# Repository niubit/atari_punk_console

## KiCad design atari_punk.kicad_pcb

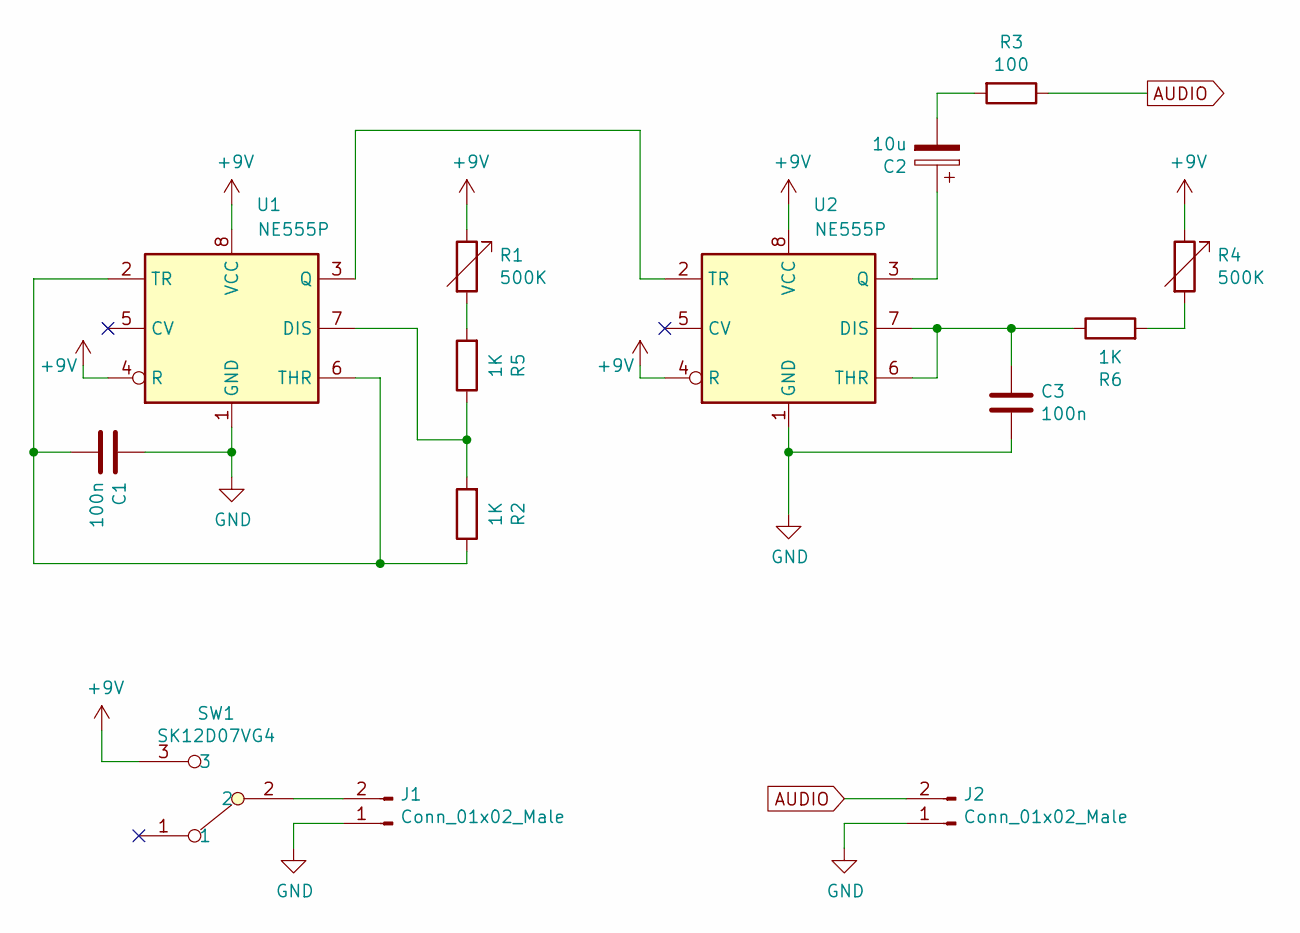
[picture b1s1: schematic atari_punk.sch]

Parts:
C1, C3: 100n; C_Disc_D4.3mm_W1.9mm_P5.00mm
C2: 10u; CP_Radial_D5.0mm_P2.50mm
J1, J2: Conn_01x02_Male; PinHeader_1x02_P2.54mm_Vertical
R1, R4: 500K; Potentiometer_Alpha_RD901F-40-00D_Single_Vertical_mod
R2, R5, R6: 1K; R_Axial_DIN0207_L6.3mm_D2.5mm_P10.16mm_Horizontal
R3: 100; R_Axial_DIN0207_L6.3mm_D2.5mm_P10.16mm_Horizontal
SW1: SK12D07VG4; SW_CuK_OS102011MA1QN1_SPDT_Angled
U1, U2: NE555P; DIP-8_W7.62mm

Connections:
+9V: R1.1, R4.1, SW1.3, U1.4 (R), U1.8 (VCC), U2.4 (R), U2.8 (VCC)
AUDIO: J2.2, R3.1
GND: C1.1, C3.2, J1.1, J2.1, U1.1 (GND), U2.1 (GND)
unnamed: C1.2, R2.1, U1.2 (TR), U1.6 (THR)
unnamed: C2.1, U2.3 (Q)
unnamed: C2.2, R3.2
unnamed: C3.1, R6.1, U2.6 (THR), U2.7 (DIS)
unnamed: J1.2, SW1.2
unnamed: R1.2, R5.2
unnamed: R2.2, R5.1, U1.7 (DIS)
unnamed: R4.2, R6.2
unnamed: U1.3 (Q), U2.2 (TR)

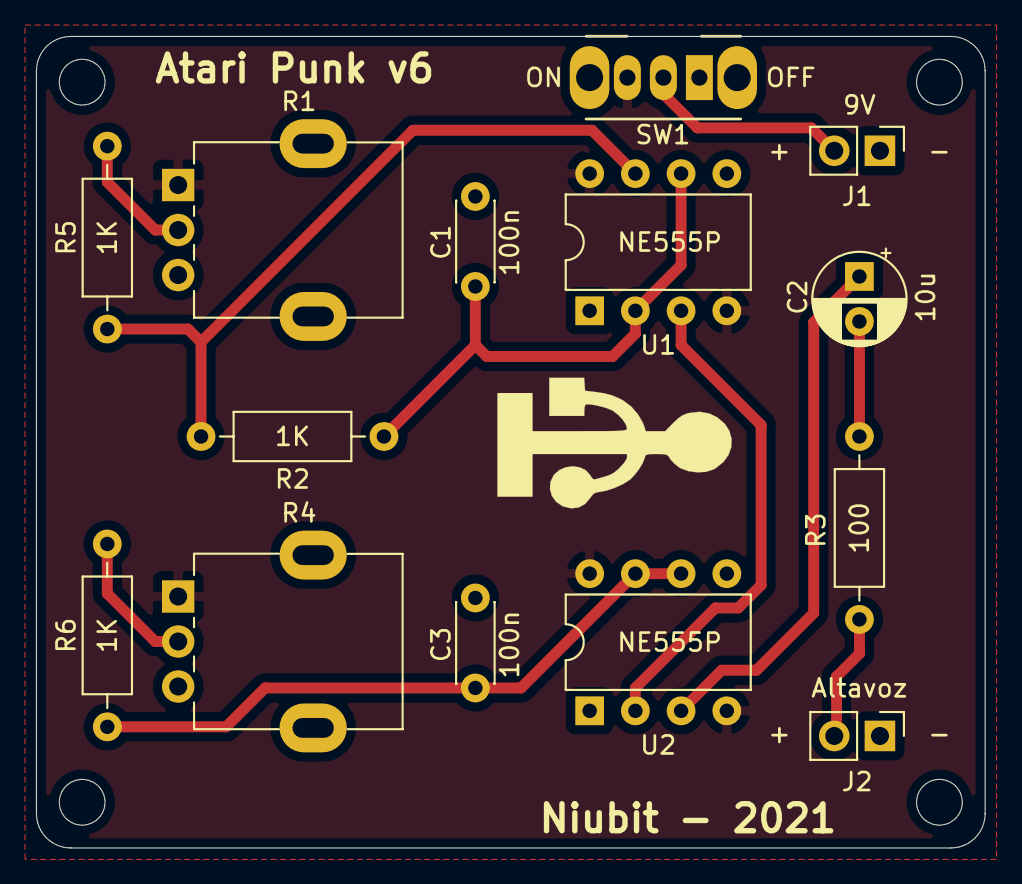
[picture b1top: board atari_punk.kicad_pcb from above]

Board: 2 copper layers, 52.7 x 45.1 mm, 14 parts (0 on the bottom side), 12 nets.

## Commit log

2020-12-28 Initial commit.
2020-12-28 Adding BOM.
2020-12-28 Update BOM.
2021-04-26 Changed Niubit logo.
2021-04-27 Added resistors. Added big Niubit logo. Added holes for mounting.
2021-04-28 Se incorpora interruptor de encendido.
2021-04-29 Cambio menor.
2021-04-29 Logo Niubit en cara inferior de 35mm de altura en lugar de 52mm.
2021-04-29 Leyenda ON/OFF.
2021-05-03 Gerbers para la v5.
2021-05-03 Borro Gerbers anteriores.
2021-05-14 Avances.
2021-07-08 Se agrandan los pad de chasis de los potenciómetros.
2021-07-14 Gerbers para v6.
2021-07-14 Faltaba hacer refill.
2021-07-14 v6 en silkscreen.
